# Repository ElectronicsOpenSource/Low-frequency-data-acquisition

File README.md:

# Low-frequency-data-acquisition
A board design with example code for data acquisition with 14-, 16-, or 18-bit resolution at 100 up to 1000 kSPS

# For more information visit OSPESA on google groups
https://groups.google.com/forum/#!forum/ospesa

Supported ADCs (to be tested):
These are all the ADCs that should be supported. The footprint used is the 10-MSOP. All ADCs are either differential or pseudo-differential (check for your application).

14-bit  -  250 kSPS  -  AD7942    -  ~$12 ea.

14-bit  -  500 kSPS  -  AD7946    -  ~$16 ea.

16-bit  -  100 kSPS  -  AD7988-1  -  ~$17 ea.

16-bit  -  250 kSPS  -  AD7685    -  ~$14 ea.     <--- I used these for now

16-bit  -  250 kSPS  -  AD7687    -  ~$19 ea.

16-bit  -  500 kSPS  -  AD7686    -  ~$24 ea.

16-bit  -  500 kSPS  -  AD7688    -  ~$29 ea.

16-bit  -  500 kSPS  -  AD7693    -  ~$35 ea.

16-bit  -  500 kSPS  -  AD7988-5  -  ~$17 ea.

16-bit  -  1000 kSPS  -  AD7980   -  ~$23 ea.

16-bit  -  1000 kSPS  -  AD7983   -  ~$34 ea.

18-bit  -  100 kSPS  -  AD7989-1  -  ~$19 ea.

18-bit  -  250 kSPS  -  AD7691    -  ~$28 ea.

18-bit  -  500 kSPS  -  AD7690    -  ~$38 ea.

18-bit  -  500 kSPS  -  AD7989-5  -  ~$25 ea.

18-bit  -  1000 kSPS  -  AD7982   -  ~$41 ea.

18-bit  -  1000 kSPS  -  AD7984   -  ~$50 ea

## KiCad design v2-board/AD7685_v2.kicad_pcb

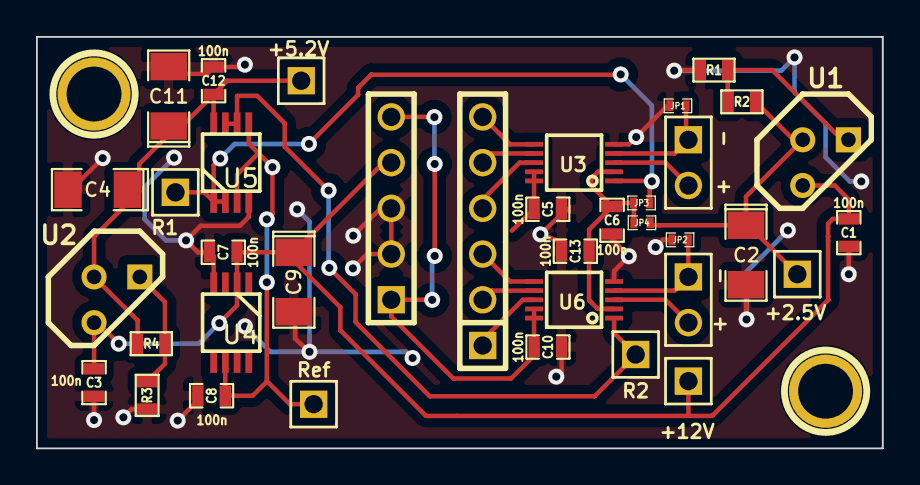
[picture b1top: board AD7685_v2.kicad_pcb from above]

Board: 2 copper layers, 47.0 x 22.9 mm, 35 parts (0 on the bottom side), 15 nets.

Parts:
+2.5V, +5.2V, +12V: CONN_1; PIN_ARRAY_1
+   -: CONN_2; PIN_ARRAY_2X1
+   -#2: CONN_2; PIN_ARRAY_2X1
C1, C3, C5, C6, C7, C8, C10, C12, C13: 100n; SM0603_Capa
C2, C4: 1u; SM1206POL
C9, C11: 10u; SM1206POL
JP1, JP2, JP3, JP4: JUMPER; SM0402
R1, R2, R4: 220R; SM0603
R1#2, R2#2: CONN_1; PIN_ARRAY_1
R3: 768R; SM0603
Ref: CONN_1; PIN_ARRAY_1
U1, U2: TO92
U3, U6: MSOP10-0.5
U4, U5: MSOP_8

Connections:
+2.5V: +2.5V.1, C2.1, JP4.2, R2.1, U1.2
+3.3V: C5.1, C10.1, U3.9, U3.10, U6.9, U6.10
+5P: +5.2V.1, C4.1, C11.1, C12.2, R4.1, U2.2, U5.8
+12V: +12V.1, C1.1, C3.1, C7.1, C9.1, U1.3, U2.3, U4.2
ADVDD: C6.2, C13.2, JP3.1, JP4.1, U3.2, U6.2
GND: C1.2, C2.2, C3.2, C4.2, C5.2, C6.1, C7.2, C8.1, C9.2, C10.2, C11.2, C12.1, C13.1, JP1.1, JP2.1, R1.2, R3.2, U3.5, U4.4, U5.4, U6.5
IN+1: + -#2.2, U3.3
IN+2: + -.2, U6.3
IN-1: + -#2.1, JP1.2, U3.4
IN-2: + -.1, JP2.2, U6.4
unnamed: R1.1, R2.2, U1.1
unnamed: R3.1, R4.2, U2.1
REF1: JP3.2, R1#2.1, U3.1, U5.1, U5.2
REF2: R2#2.1, U5.6, U5.7, U6.1
Vadr: C8.2, Ref.1, U4.6, U5.3, U5.5

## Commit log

2015-01-19 Added these for documentation purposes only
2015-01-19 Schematic, board layout and Gerber files
2015-01-20 VHDL code to test the AD7865 ADC at 250 kSPS
    Uses a 20 MHz clock to achieve 250 kSPS
    8192 samples are read and then output to a PC via RS232
